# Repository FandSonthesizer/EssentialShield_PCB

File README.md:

# EssentialShield_PCB
STM32F103c based shield for digital and analog input and output

This shield is a very powerful tool for multiple purposes. It can be used in all kinds of applications, where you 
need analog input and analog output as well as digital in- and output. We use it very much in our audio applications.
It is prepared for a display and and encoder and it can receive and send MIDI signals.

Specs: 
- Based on a cheap 'Blue-Pill' stm32f103c shield.
- Up to 4 Analog outputs in the range of 0-10V
- 8 analog /digital inputs (0-3.3V)
- 4 Digital outputs (0-5V)
- 3 digital inputs (0-3.3V)
- 1 Gate/Trigger input (0-10V)
- Midi in/out
- Connector for KY 040 Encoder
- Connector for SPI OLED display e.g. 128x64 pixel black and white OLED
- Connector for USB to TTL adapter
- Eurorack power connector (2 x 8 pin)

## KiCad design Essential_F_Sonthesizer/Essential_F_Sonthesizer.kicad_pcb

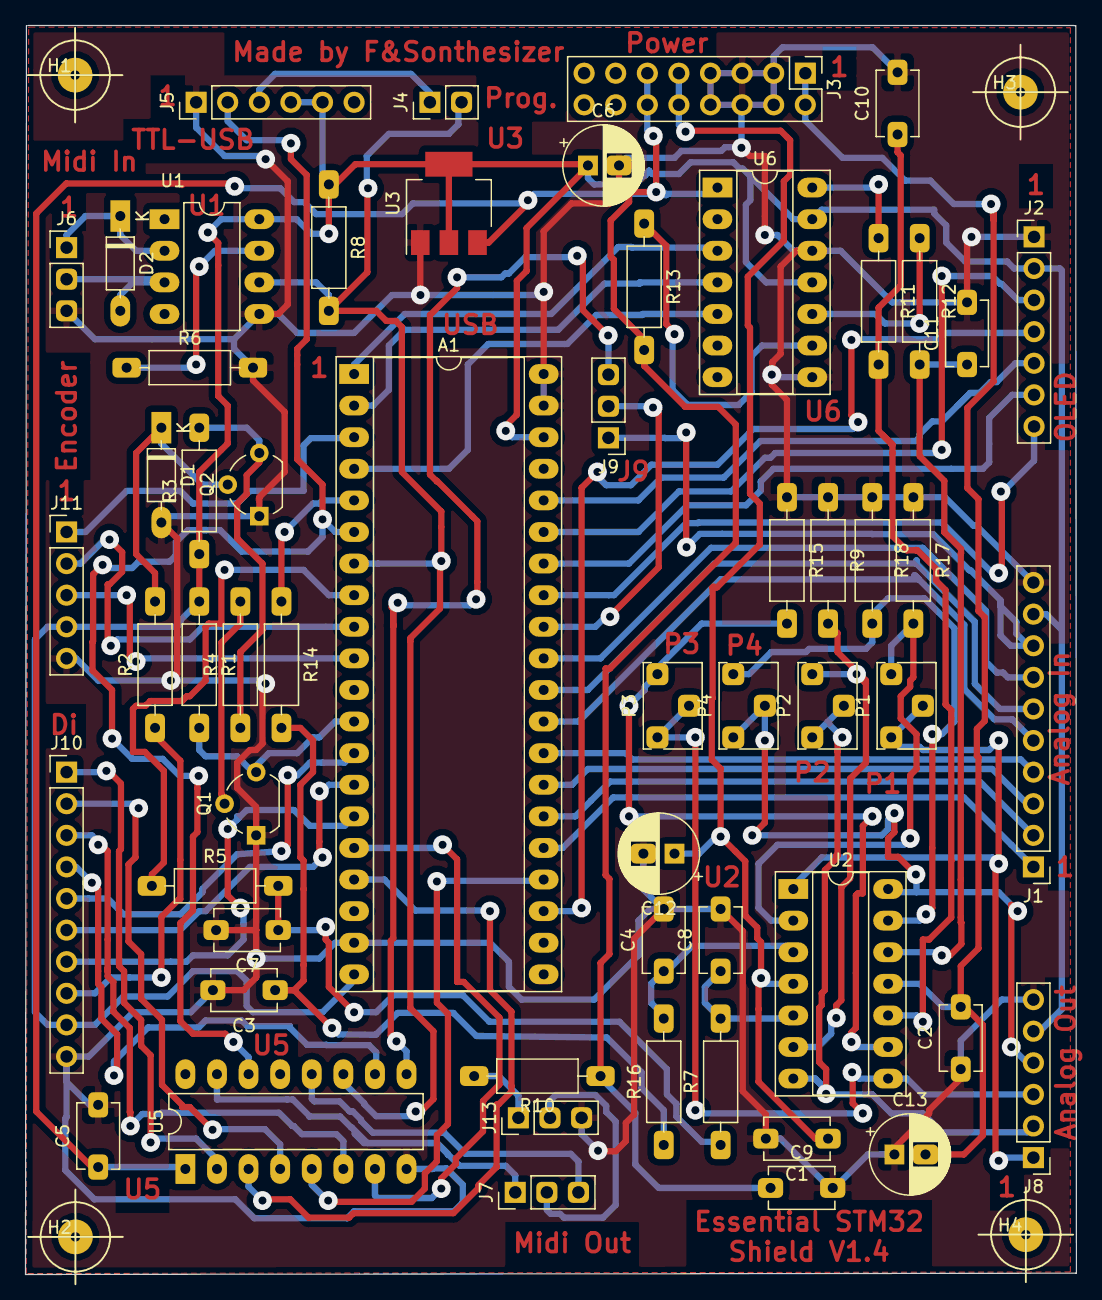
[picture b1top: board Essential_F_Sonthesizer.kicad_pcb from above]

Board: 2 copper layers, 84.5 x 100.4 mm, 61 parts (0 on the bottom side), 69 nets.

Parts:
A1: Blue_Pill; DIP-40_W15.24mm_Socket_LongPads
C1, C2, C5, C9: 100n; Kondensator_Keramik
C3, C7: 33n; Kondensator_Keramik
C4, C8, C10, C11: 1n; Kondensator_Keramik
C6, C12, C13: 47u; Elko_D6.3mm_P2.50mm
D1, D2: 1N4148; Diode_Horizontal
H1, H2, H3, H4: MountingHole; MountHole
J1: AnalogIn; PinHeader_1x10_P2.54mm_Vertical
J2: SPI Display Oled; PinHeader_1x07_P2.54mm_Vertical
J3: Power Con; PinHeader_2x08_P2.54mm_Vertical
J4: Programm Jumper; Stift_x02
J5: TTL-USB; PinHeader_1x06_P2.54mm_Vertical
J6: Midi In; Stift_0x3
J7: Midi-OUT-Through; Stift_0x3
J8: Analog Out; PinHeader_1x06_P2.54mm_Vertical
J9: Pa7-Out4 Jumper; Stift_0x3
J10: Digital; PinHeader_1x10_P2.54mm_Vertical
J11: Encoder; PinHeader_1x05_P2.54mm_Vertical
J13: Midi Out; Stift_0x3
P1, P2: 20k; Trimmer_Vertical
P3, P4: 47k; Trimmer_Vertical
Q1, Q2: 2N3904; TO-92_Wide
R1, R3: 4.7k; Widerstand_liegend
R2, R7, R9, R11, R12, R13, R15, R16, R17, R18: 10k; Widerstand_liegend
R4: 22k; Widerstand_liegend
R5, R14: 2,2k; Widerstand_liegend
R6: 3.3k; Widerstand_liegend
R8: 1k; Widerstand_liegend
R10: 220; Widerstand_liegend
U1: 6N138; DIP-8_W7.62mm_LongPads
U2: TL074; DIP-14_W7.62mm_Socket_LongPads
U3: AMS1117-3.3; SOT-223-3Lead_TabPin2
U5: 4050; DIP-16_W7.62mm_LongPads
U6: MCP4922; DIP-14_W7.62mm_Socket_LongPads

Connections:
3.3V: A1.20, A1.38, C6.1, J1.9, J2.2, J5.4, J5.5, J8.5, J10.9, J11.4, R1.1, R3.1, R8.1, U1.8, U3.2, U6.11, U6.13
+5V: C5.1, C9.1, J3.11, J3.12, R10.1, R13.2, U3.3, U5.1, U6.1
+12V: C1.1, C12.1, J3.9, J3.10, U2.4
-12V: C2.2, C13.2, J3.1, J3.2, U2.11
AnalogIn0: A1.25, J1.1
AnalogIn1: A1.26, J1.2
AnalogIn2: A1.27, J1.3
AnalogIn3: A1.28, J1.4
AnalogIn4: A1.29, J1.5
AnalogIn5: A1.30, J1.6
AnalogIn6: A1.31, J1.7
AnalogIn7: J1.8, J9.1
AnalogOut1: J8.1, P1.2, P1.3, U2.1
AnalogOut2: J8.2, P2.2, P2.3, U2.7
AnalogOut3: J8.3, P3.2, P3.3, U2.8
AnalogOut4: J8.4, P4.2, P4.3, U2.14
CLK-KY040: A1.3, J11.1
ClockIn: A1.12, Q1.3, R1.2
DAC0: R11.1, U6.14
DAC1: R12.1, U6.10
DAC_CS: A1.1, U6.3
DAC_SCK: A1.2, U6.4
DAC_SDI: A1.4, U6.5
DT-KY040: A1.9, J11.2
GND: A1.19, A1.39, A1.40, C1.2, C2.1, C3.2, C4.2, C5.2, C6.2, C7.2, C8.2, C9.2, C10.2, C11.2, C12.2, C13.1, D1.2, J1.10, J2.1, J3.3, J3.4, J3.5, J3.6, J3.7, J3.8, J5.1, J6.3, J8.6, J10.10, J11.5, J13.3, Q1.1, Q2.1, R6.2, R9.1, R15.1, R17.1, R18.1, U1.5, U3.1, U5.8, U6.8, U6.12
Input1: A1.13, J10.5
Input2: A1.14, J10.6
Input3: A1.15, J10.7
unnamed: C3.1, R14.2, R16.1
unnamed: C4.1, R16.2, U2.3
unnamed: C7.1, R5.2, R7.1
unnamed: C8.1, R7.2, U2.5
unnamed: C10.1, R11.2, U2.10
unnamed: C11.1, R12.2, U2.12
unnamed: D1.1, Q2.2, R2.2
unnamed: D2.1, J6.1, U1.2
unnamed: D2.2, J6.2, U1.3
unnamed: J4.1, J5.3
unnamed: J7.1, U5.15
unnamed: J7.3, U5.12
unnamed: J13.1, R10.2
unnamed: J7.2, J13.2
unnamed: P1.1, R17.2, U2.2
unnamed: P2.1, R9.2, U2.6
unnamed: P3.1, R15.2, U2.9
unnamed: P4.1, R18.2, U2.13
unnamed: Q1.2, R4.2
unnamed: Q2.3, R3.2, R4.1
unnamed: R6.1, U1.7
unnamed: R13.1, U6.9
O1: J10.1, U5.2
O2: J10.2, U5.4
O3: J10.3, U5.6
O4: J10.4, U5.10
OLED-CS: A1.33, J2.7
OLED-D0: A1.35, J2.3
OLED-D1: A1.23, J2.4
OLED-DC: A1.34, J2.6
OLED-Res: A1.36, J2.5
Out1: A1.17, U5.3
Out2: A1.24, U5.5
Out3: A1.16, U5.7
PA7: A1.32, J9.2
PWMOut: A1.5, R14.1
PWMOut2: A1.8, R5.1
RxD: A1.7, J4.2, R8.2, U1.6, U5.11
SW-KY040: A1.10, J11.3
Trigger: J10.8, R2.1
TxD: A1.6, J5.2, U5.14
